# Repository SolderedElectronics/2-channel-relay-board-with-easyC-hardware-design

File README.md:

# 2-channel relay board with easyC Hardware design

## About the product

|  |
| :----------------------------------------------------------: |
|      [Buy 2-channel relay board with easyC](https://www.solde.red/333025)      |

Did you ever wanted to turn on and off a device that needs large current or voltage? Whether operating on DC or AC, a relay is what you need. A relay is actually an electronic switch that is activated by a signal we send from a Dasduino or Arduino. This module further simplifies the whole process because it contains everything you need for the relay to work, and you just have to connect it to the microcontroller and power supply. You don’t have to think about voltages and currents, insulation between high and low voltage or grounding, everything is already taken care of on the board.

This board has easyC connector. Thanks to easyC ecosystem, this board can be connected using off-the-shelf cables, without soldering. Controlling the is as simple as it gets, too. Learn more about easyC here.

## Repository contents

All Soldered Electronics hardware designed in KiCAD, and repositories are organized in the following way:

- CAD folder - contains KiCAD files (Schematics, Board, Panel Board), sorted by version. Change log lists all changes between versions.
- OUTPUTS - contains useful files, such as Bill of Materials (BOM), PDF of schematics, 3D .step file of the board and gerber files, sorted by version. 
- OUTPUTS -> Compliance - Certificates and useful legal stuff. 

## Want to contribute?

Please feel free to submit a pull request if you have any contributions. We encourage you to submit an issue or pull request if you find a bug. 

## About Soldered

At Soldered, we design and manufacture a wide selection of electronic products to help you turn your ideas into acts and bring you one step closer to your final project. Our products are intented for makers and crafted in-house by our experienced team in Osijek, Croatia. We believe that sharing is a crucial element for improvement and innovation, and we work hard to stay connected with all our makers regardless of their skill or experience level. Therefore, all our products are open-source. Finally, we always have your back. If you face any problem concerning either your shopping experience or your electronics project, our team will help you deal with it, offering efficient customer service and cost-free technical support anytime. Some of those might be useful for you:

- [Web Store](https://www.soldered.com/shop)
- [Tutorials & Projects](https://soldered.com/learn)
- [Community & Technical support](https://soldered.com/community)

## License info

All Soldered open-source hardware (OSH) is under The TAPR Open Hardware License. Read more in the LICENSE file. 

No warranty - all designs in this repository are distributed in the hope that they will be useful, but without any warranty. They are provided "AS IS", therefore without warranty of any kind, either expressed or implied. The entire quality and performance of what you do with the contents of this repository are your responsibility. In no event, Soldered Electronics will be liable for your damages, losses, including any general, special, incidental or consequential damage arising out of the use or inability to use the contents of this repository. 

## Have fun! 
And thank you from your fellow makers at Soldered Electronics.

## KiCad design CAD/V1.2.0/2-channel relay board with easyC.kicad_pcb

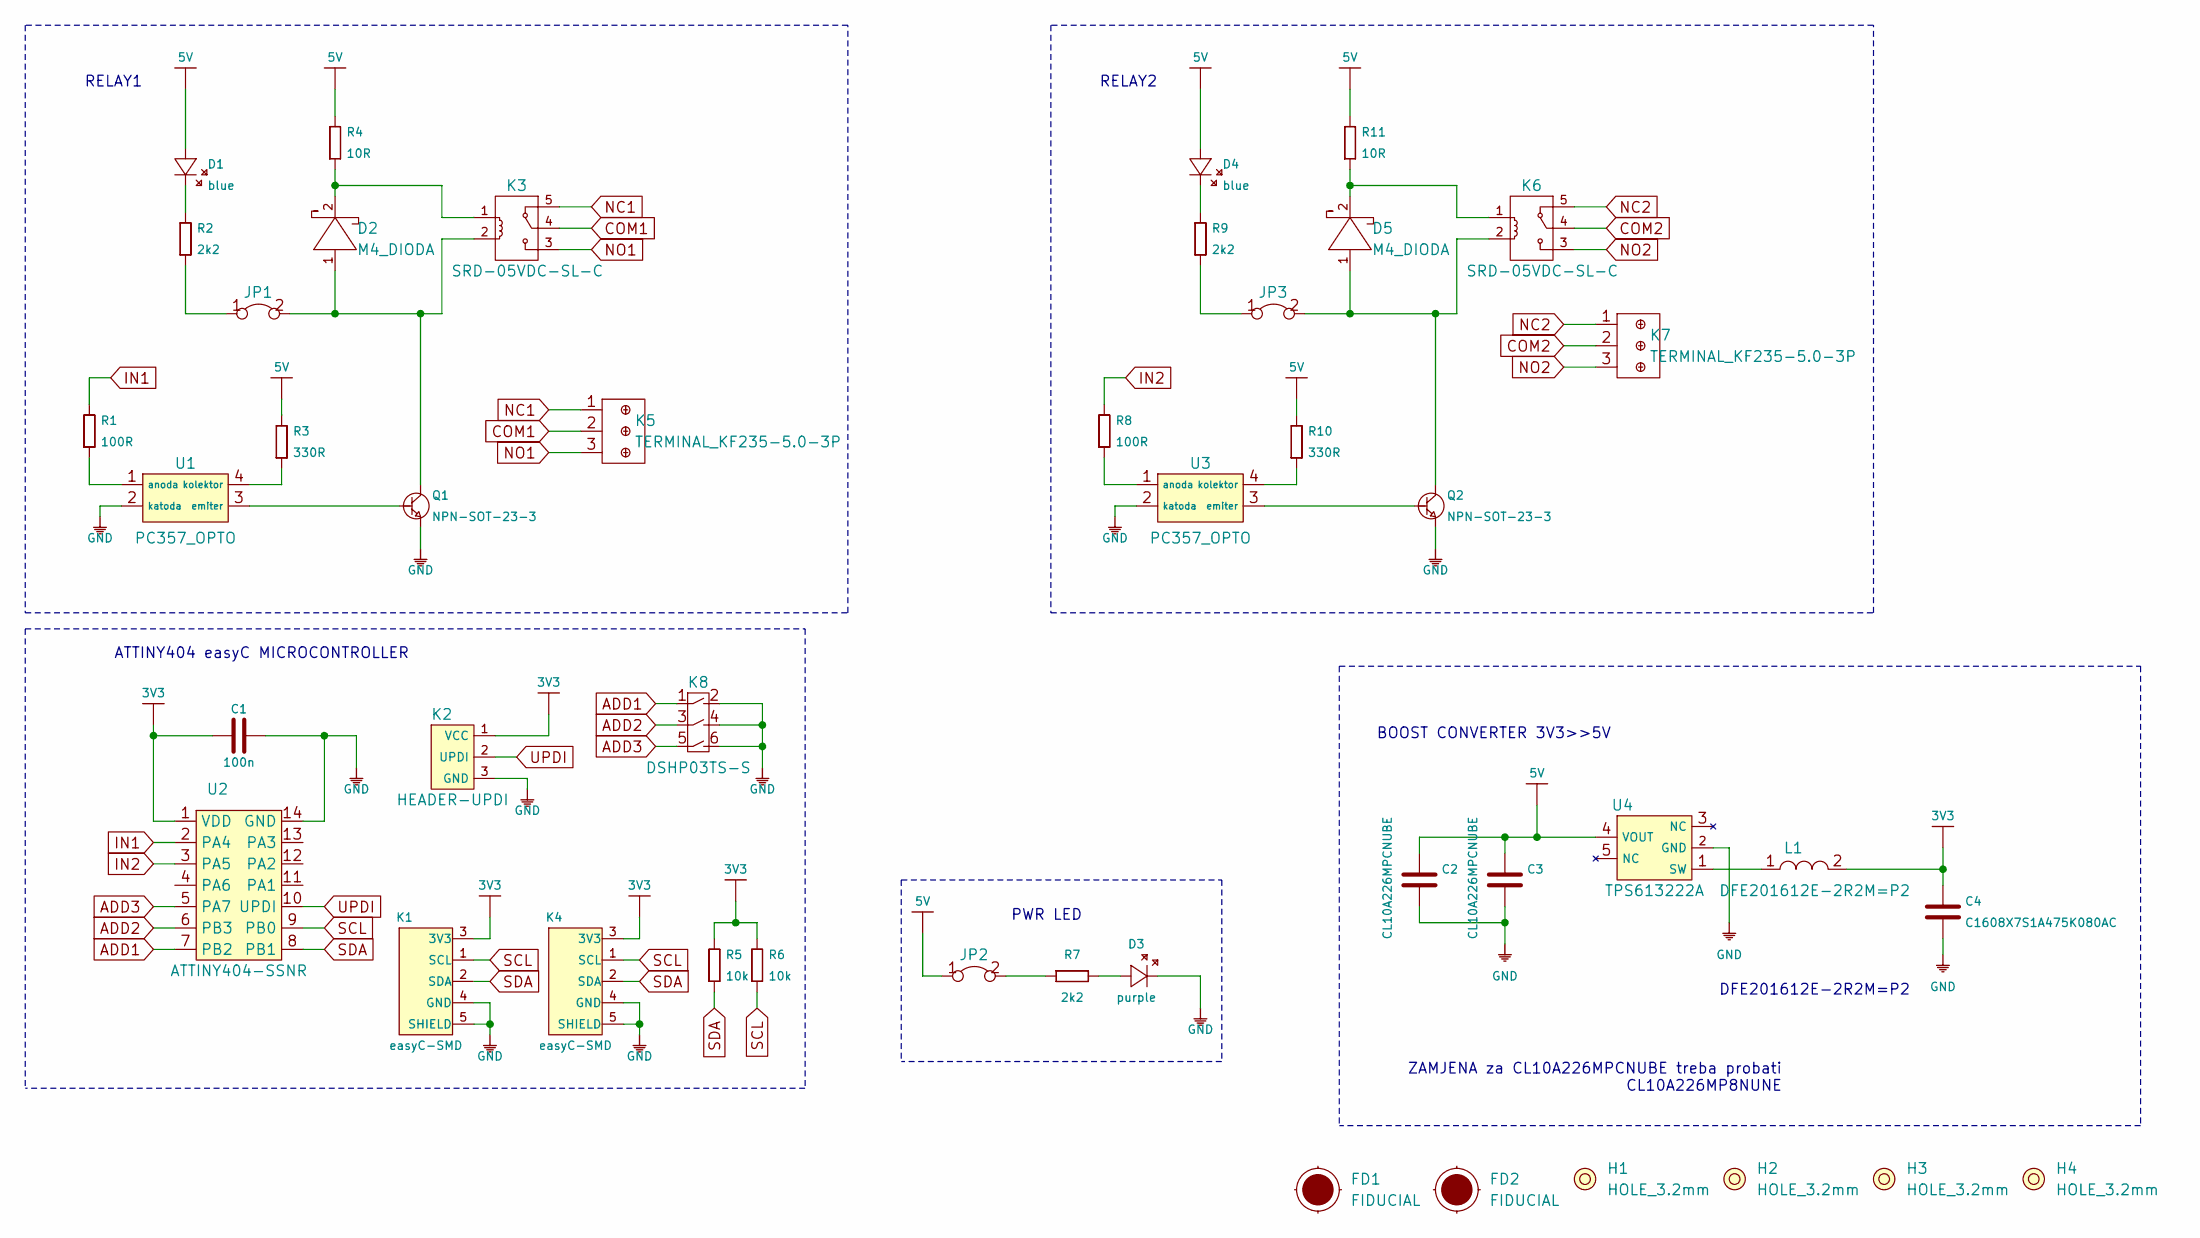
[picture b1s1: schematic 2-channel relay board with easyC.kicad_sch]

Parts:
C1: 100n; 0603C
C2, C3: CL10A226MPCNUBE; 0603C
C4: C1608X7S1A475K080AC; 0603C
D1, D4: blue; 0402LED
D2, D5: M4_DIODA
D3: purple; 0402LED
FD1, FD2: FIDUCIAL; FIDUCIAL_23
H1, H2, H3, H4: HOLE_3.2mm
JP1, JP2, JP3: SMD-JUMPER-CONNECTED_TRACE_SLODERMASK
K1, K4: easyC-SMD; easyC-connector
K2: HEADER-UPDI
K3, K6: SRD-05VDC-SL-C; SRD_RELAY_5V
K5, K7: TERMINAL_KF235-5.0-3P
K8: DSHP03TS-S
L1: DFE201612E-2R2M=P2; 0806L
Q1, Q2: NPN-SOT-23-3; SOT-23-3
R1, R8: 100R; 0603R
R2, R7, R9: 2k2; 0402R
R3, R10: 330R; 0603R
R4, R11: 10R; 0603R
R5, R6: 10k; 0603R
U1, U3: PC357_OPTO
U2: ATTINY404-SSNR; SOIC-14
U4: TPS613222A; tps613222a

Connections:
3V3: C1.1, C4.2, K1.3 (3V3), K2.1 (VCC), K4.3 (3V3), L1.2, R5.2, R6.2, U2.1 (VDD)
5V: C2.2, C3.2, D1.1 (A), D4.1 (A), JP2.1, R3.2, R4.2, R10.2, R11.2, U4.4 (VOUT)
ADD1: K8.1, U2.7 (PB2)
ADD2: K8.3, U2.6 (PB3)
ADD3: K8.5, U2.5 (PA7)
COM1: K3.4, K5.2
COM2: K6.4, K7.2
GND: C1.2, C2.1, C3.1, C4.1, D3.2 (K), K1.4 (GND), K1.5 (SHIELD), K2.3 (GND), K4.4 (GND), K4.5 (SHIELD), K8.2, K8.4, K8.6, Q1.2 (E), Q2.2 (E), U1.2 (katoda), U2.14 (GND), U3.2 (katoda), U4.2 (GND)
IN1: R1.2, U2.2 (PA4)
IN2: R8.2, U2.3 (PA5)
NC1: K3.5, K5.1
NC2: K6.5, K7.1
NO1: K3.3, K5.3
NO2: K6.3, K7.3
unnamed: D1.2 (K), R2.2
unnamed: D2.1 (A), JP1.2, K3.2, Q1.3 (C)
unnamed: D2.2 (K), K3.1, R4.1
unnamed: D3.1 (A), R7.2
unnamed: D4.2 (K), R9.2
unnamed: D5.1 (A), JP3.2, K6.2, Q2.3 (C)
unnamed: D5.2 (K), K6.1, R11.1
unnamed: JP1.1, R2.1
unnamed: JP2.2, R7.1
unnamed: JP3.1, R9.1
unnamed: L1.1, U4.1 (SW)
unnamed: Q1.1 (B), U1.3 (emiter)
unnamed: Q2.1 (B), U3.3 (emiter)
unnamed: R1.1, U1.1 (anoda)
unnamed: R3.1, U1.4 (kolektor)
unnamed: R8.1, U3.1 (anoda)
unnamed: R10.1, U3.4 (kolektor)
SCL: K1.1 (SCL), K4.1 (SCL), R6.1, U2.9 (PB0)
SDA: K1.2 (SDA), K4.2 (SDA), R5.1, U2.8 (PB1)
UPDI: K2.2 (UPDI), U2.10 (UPDI)

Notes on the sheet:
DFE201612E-2R2M=P2
PWR LED
ATTINY404 easyC MICROCONTROLLER
RELAY2
BOOST CONVERTER 3V3>>5V
ZAMJENA za CL10A226MPCNUBE treba probati CL10A226MP8NUNE
RELAY1

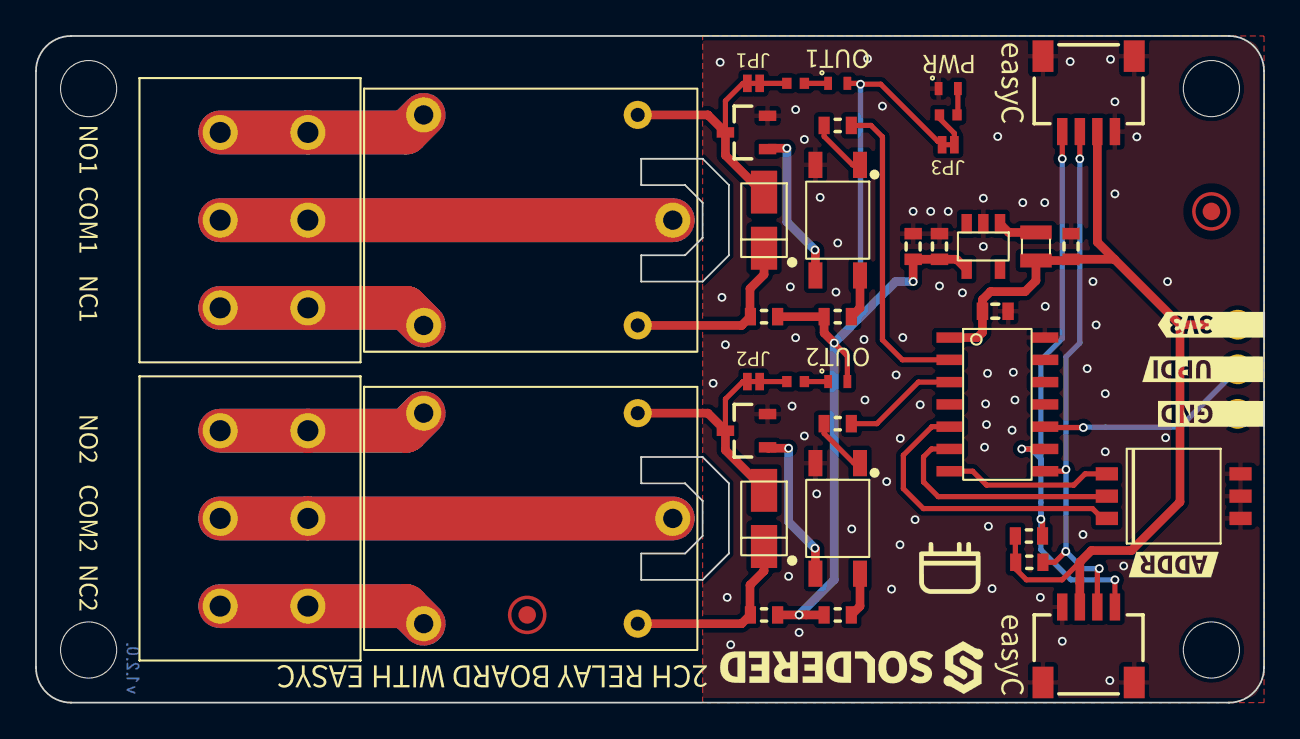
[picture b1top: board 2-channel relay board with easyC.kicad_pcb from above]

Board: 2 copper layers, 70.0 x 38.0 mm, 61 parts (0 on the bottom side), 34 nets.

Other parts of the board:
kibuzzard-66471C86: G***; kibuzzard-66471C86
kibuzzard-66471D8F: G***; kibuzzard-66471D8F
kibuzzard-66471D63: G***; kibuzzard-66471D63
kibuzzard-66471D78: G***; kibuzzard-66471D78
kibuzzard-66471D83: G***; kibuzzard-66471D83
kibuzzard-66471DA3: G***; kibuzzard-66471DA3
kibuzzard-66471DBB: G***; kibuzzard-66471DBB
kibuzzard-66471E5D: G***; kibuzzard-66471E5D
kibuzzard-66471E6B: G***; kibuzzard-66471E6B
kibuzzard-66471E22: G***; kibuzzard-66471E22
kibuzzard-66471E33: G***; kibuzzard-66471E33
kibuzzard-66471E46: G***; kibuzzard-66471E46
kibuzzard-66471E80: G***; kibuzzard-66471E80
kibuzzard-66471EBB: G***; kibuzzard-66471EBB
kibuzzard-66471ED2: G***; kibuzzard-66471ED2
kibuzzard-66471EE5: G***; kibuzzard-66471EE5
kibuzzard-66471EEF: G***; kibuzzard-66471EEF

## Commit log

2022-08-06 Updating open source files.
